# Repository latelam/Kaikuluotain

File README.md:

Näyttää ultraäänisensorin ja kohteen välisen etäisyyden LCD-näytöllä ja sarjamonitorissa, 0,1mm tarkkuudella. Alue 2cm-4metriä.

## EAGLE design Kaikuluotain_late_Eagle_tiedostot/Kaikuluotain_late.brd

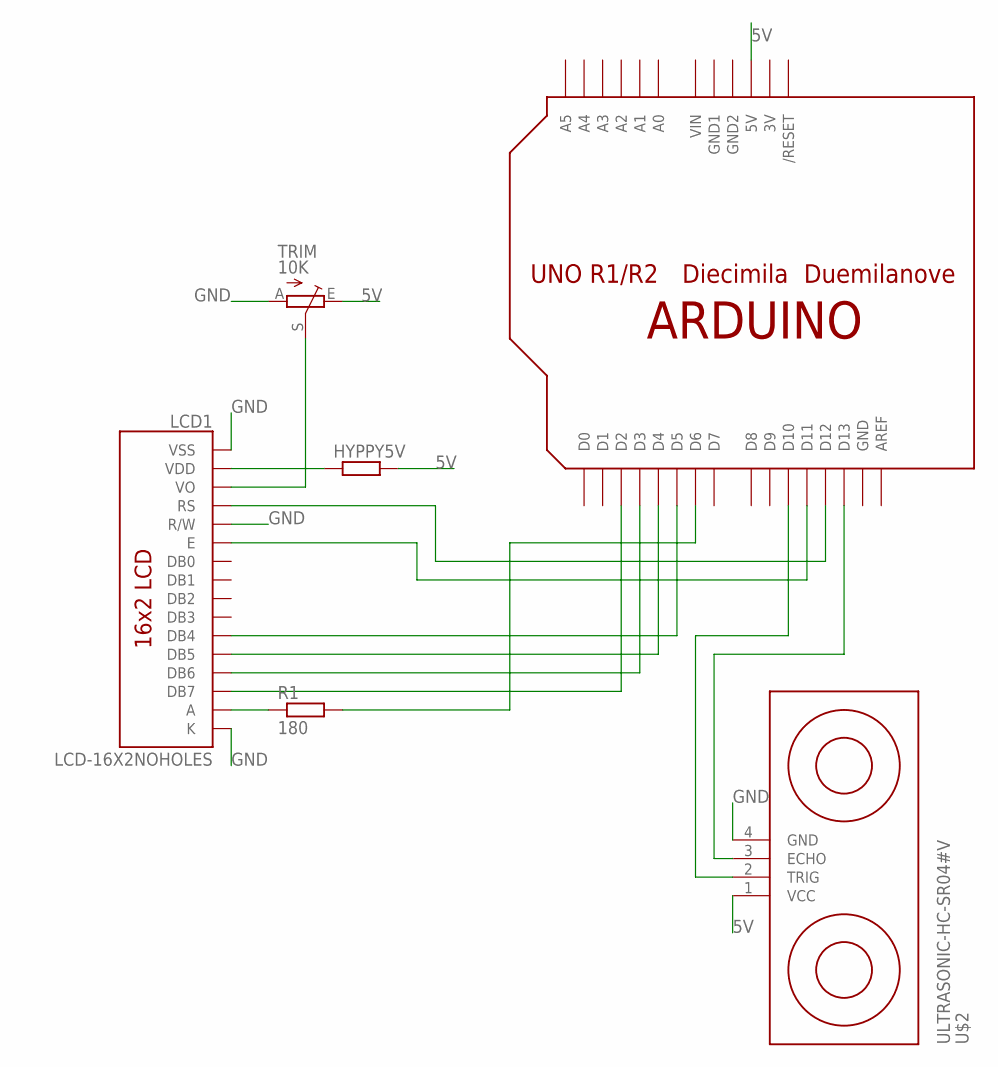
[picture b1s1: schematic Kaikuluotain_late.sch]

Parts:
HYPPY5V: R-EU_0207/10; 0207/10
LCD1: LCD-16X2NOHOLES; LCD-16X2_NOHOLESNOSILK
R1: 180; 0411/15
TRIM: 10K; CA9V
U$1: ARDUINO-NOHOLE
U$2: ULTRASONIC-HC-SR04#V

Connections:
3V: U$1.3V
5V: HYPPY5V.2, TRIM.E, U$1.5V, U$2.1 (VCC)
GND: LCD1.1 (VSS), LCD1.5 (R/W), LCD1.16 (K), TRIM.A, U$1.GND, U$2.4 (GND)
GND1: U$1.GND1
GND2: U$1.GND2
unnamed: LCD1.15 (A), R1.1
unnamed: U$1.D13, U$2.3 (ECHO)
unnamed: U$1.D10, U$2.2 (TRIG)
unnamed: LCD1.3 (VO), TRIM.S
unnamed: LCD1.4 (RS), U$1.D12
unnamed: LCD1.6 (E), U$1.D11
unnamed: LCD1.11 (DB4), U$1.D5
unnamed: LCD1.12 (DB5), U$1.D4
unnamed: LCD1.13 (DB6), U$1.D3
unnamed: LCD1.14 (DB7), U$1.D2
unnamed: R1.2, U$1.D6
unnamed: HYPPY5V.1, LCD1.2 (VDD)
VIN: U$1.VIN

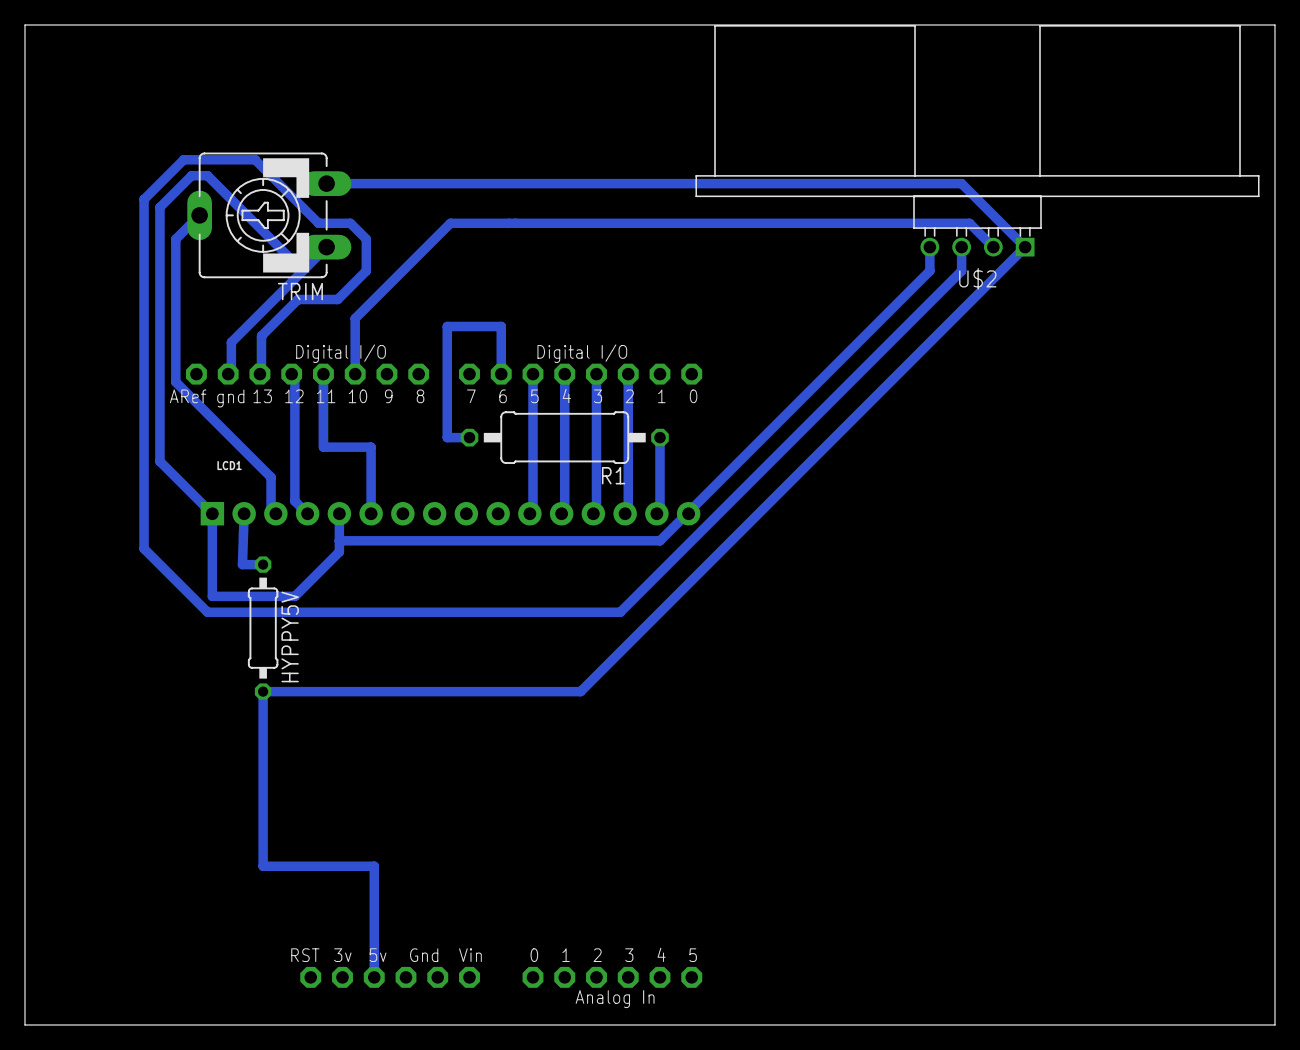
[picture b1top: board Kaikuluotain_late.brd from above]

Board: 2 copper layers, 100.0 x 80.0 mm, 6 parts (0 on the bottom side), 14 nets.

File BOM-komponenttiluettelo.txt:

Partlist exported from D:/Sulautetut_nayttotyo2018/Kaikuluotain/Kaikuluotain_late_Eagle_tiedostot/Kaikuluotain_late.sch at 17.12.2018 17.26

Qty Value                Device               Package                Parts   Description                                SF_ID     SPICEPREFIX
1                        R-EU_0207/10         0207/10                HYPPY5V RESISTOR, European symbol                            R          
1   10K                  TRIM_EU-CA9V         CA9V                   TRIM    POTENTIOMETER                                                   
1   180                  R-EU_0411/15         0411/15                R1      RESISTOR, European symbol                                       
1   ARDUINO-NOHOLE       ARDUINO-NOHOLE       ARDUINO-NOHOLE         U$1     Arduino Diecimila/Duemilanove                                   
1   LCD-16X2NOHOLES      LCD-16X2NOHOLES      LCD-16X2_NOHOLESNOSILK LCD1    Standard text-only 16x2 parallel input LCD LCD-00255            
1   ULTRASONIC-HC-SR04#V ULTRASONIC-HC-SR04#V ULTRASONIC-HC-SR04#V   U$2     Ultrasonic Ranging Module HC-SR04

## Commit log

2018-11-27 LCD lisätty
2018-11-29 LCD:n taustavalon on/off-ohjaus liitetty ja Eagle-tiedostoja.
2018-12-01 Lisätty alkudemo ja laskutoimitukselle oma funktio kirjastoon.
2018-12-03 Tein Ääkköset.
2018-12-04 Valmis
2018-12-13 Kaikuluotain
    Näyttää ultraäänisensorin ja kohteen välisen etäisyyden LCD-näytöllä sekä sarjaportissa, 0,1mm tarkkuudella.

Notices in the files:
parts and their libraries:
SparkFun-Displays: Licensing: Creative Commons ShareAlike 4.0 International - https://creativecommons.org/licenses/by-sa/4.0
diy-modules: Released under the Creative Commons Attribution 4.0 International License: http://creativecommons.org/licenses/by/4.0
